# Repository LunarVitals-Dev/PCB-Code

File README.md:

## Overview
This project utilizes the Nordic nRF52840 and various sensors for data collection and analysis. Below are the sensors used, their datasheets, and their respective pin connections.

## Sensors and Connections

### On-Board Sensors (Connected to PCB)

1. **MLX90614 (Infrared Temperature Sensor)**  
   - [Datasheet](https://www.melexis.com/en/documents/documentation/datasheets/datasheet-mlx90614)  
   - **Connections:**
     - SDA -> P0.13
     - SCL -> P0.15
     - VDD -> VDD
     - GND -> GND

2. **MPU6050 (Accelerometer & Gyroscope)**  
   - [Datasheet](https://invensense.tdk.com/wp-content/uploads/2015/02/MPU-6000-Datasheet1.pdf)  
   - **Connections:**
     - SDA -> P1.10
     - SCL -> P1.15
     - VDD -> VDD
     - GND -> GND

3. **BMP280 (Barometric Pressure Sensor)**  
   - [Datasheet](https://cdn-shop.adafruit.com/datasheets/BST-BMP280-DS001-11.pdf)   
   - **Connections:**
     - SDI -> P0.13
     - SCK -> P0.15
     - SDO -> VDD
     - 3Vo -> VDD
     - GND -> GND

### External Sensors (Connected Externally)

4. **MAX30102 (Heart Rate & Blood Oxygen Sensor)**  
   - [Datasheet](https://www.analog.com/media/en/technical-documentation/data-sheets/max30102.pdf)  
   - **Connections:**
     - SDA -> P0.13
     - SCL -> P0.15
     - VDD -> VDD
     - GND -> GND

5. **SEN-11754 (Pulse Sensor)**  
   - [Datasheet](https://www.digikey.com/en/products/detail/sparkfun-electronics/SEN-11574/5762397)  
   - **Connections:**
     - ADC -> P0.29
     - VDD -> VDD
     - GND -> GND

6. **Conductive Rubber Cord (Stretch Sensor)**  
   - [Datasheet](https://www.verical.com/datasheet/adafruit-misc-sensors-519-5047094.pdf)  
   - **Connections:**
     - ADC -> P0.31
     - VDD -> VDD
     - GND -> GND

7. ADC: AIN5 - 0.29 (Pulse Sensor), AIN7 - 0.31 (Rubber Cord)

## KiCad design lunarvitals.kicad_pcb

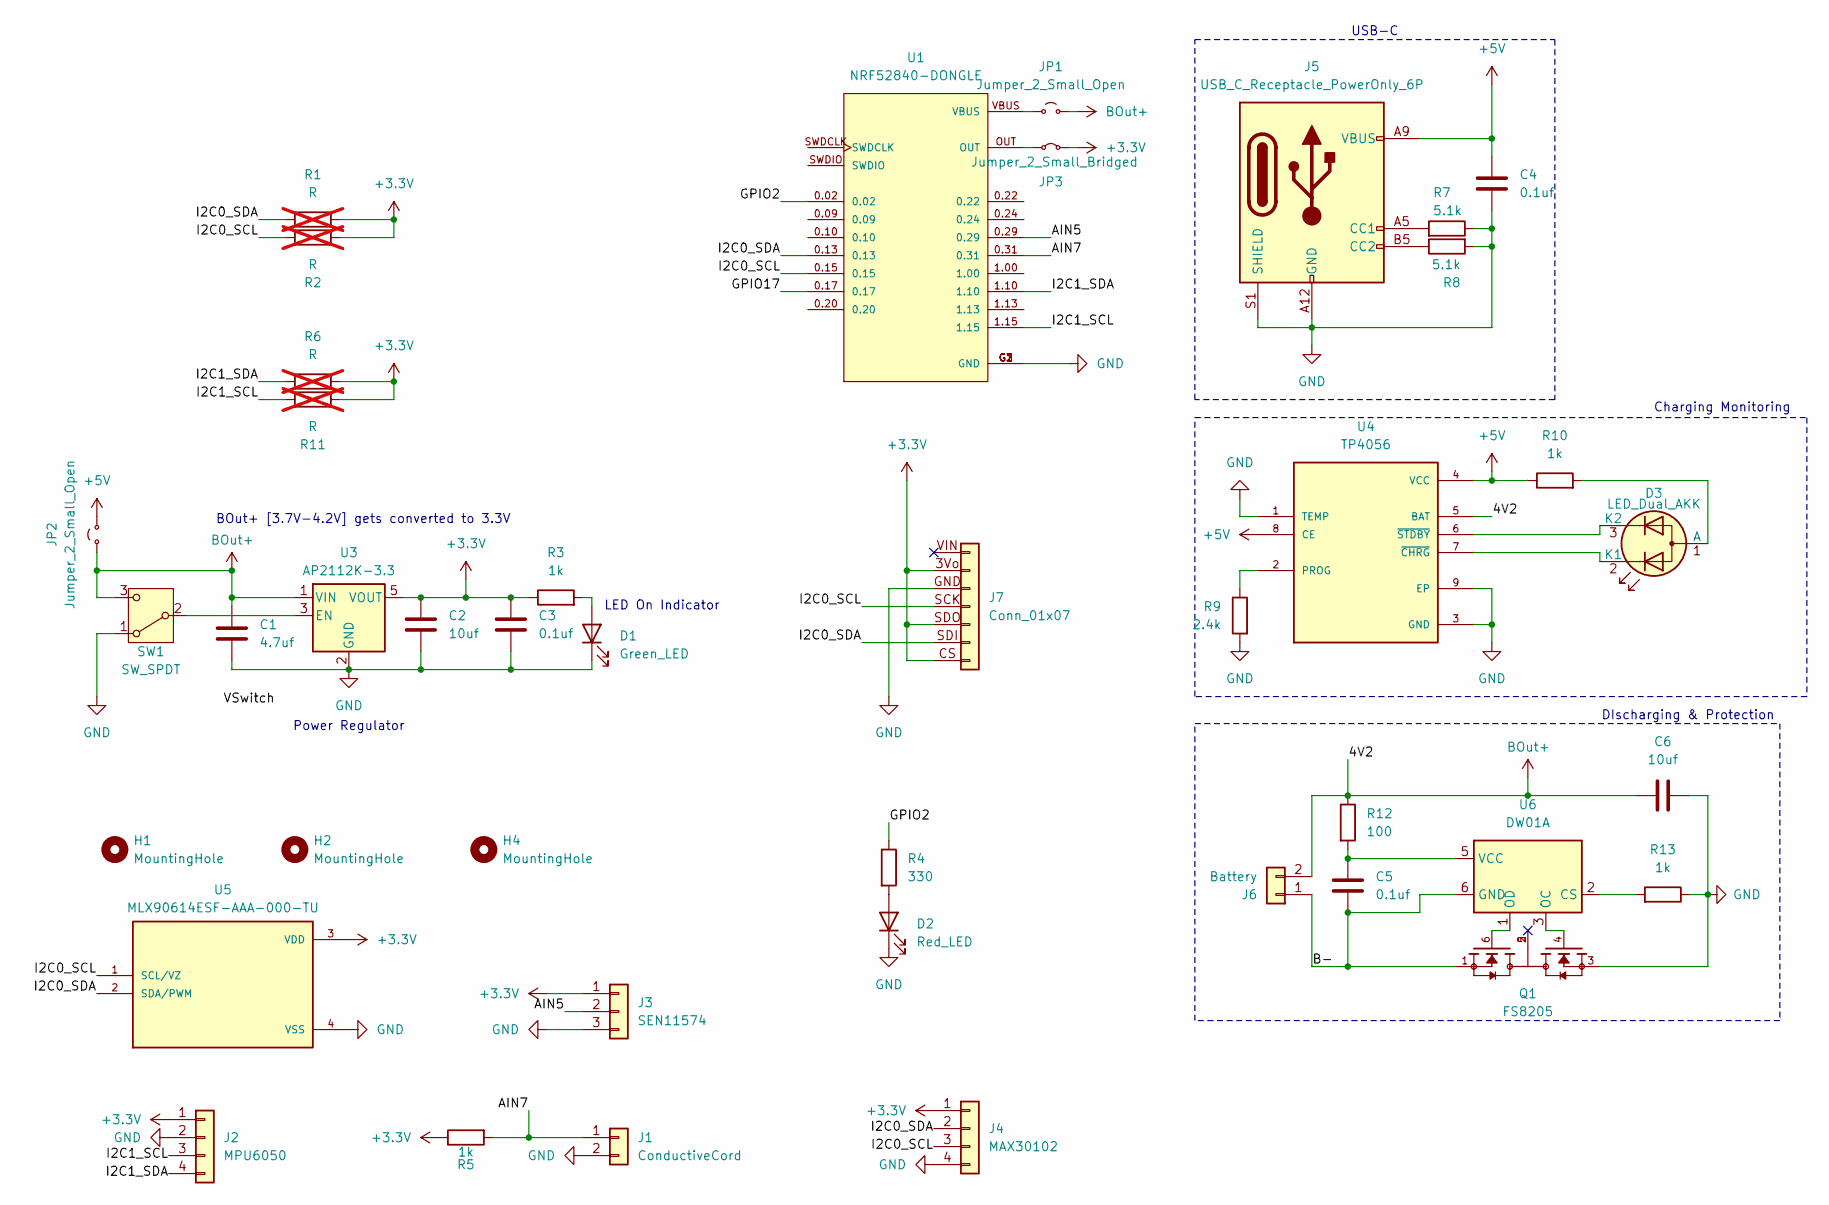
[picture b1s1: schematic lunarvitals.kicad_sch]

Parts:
C1: 4.7uf; C_0402_1005Metric; LCSC C23733
C2, C6: 10uf; C_0402_1005Metric; LCSC C15525
C3, C4, C5: 0.1uf; C_0402_1005Metric; LCSC C1525
D1: Green_LED; LED_D3.0mm
D2: Red_LED; LED_D3.0mm
D3: LED_Dual_AKK; LED_Kingbright_APBA3010SURKCGKC-GX_3x2x1mm; LCSC C5875732
H1, H2, H4: MountingHole; MountingHole_2.2mm_M2
J1: ConductiveCord; JST_XH_B2B-XH-A_1x02_P2.50mm_Vertical; LCSC C158012
J2: MPU6050; JST_XH_B4B-XH-A_1x04_P2.50mm_Vertical; LCSC C144395
J3: SEN11574; JST_XH_B3B-XH-A_1x03_P2.50mm_Vertical; LCSC C144394
J4: MAX30102; JST_XH_B4B-XH-A_1x04_P2.50mm_Vertical; LCSC C144395
J5: USB_C_Receptacle_PowerOnly_6P; USB_C_Receptacle_GCT_USB4125-xx-x-0190_6P_TopMnt_Horizontal; LCSC C668623
J6: Battery; SM02B-SRSS-TB_LF__SN_; LCSC C160402
J7: Conn_01x07; bmp280breakout
JP1, JP2: Jumper_2_Small_Open; SolderJumper-2_P1.3mm_Open_RoundedPad1.0x1.5mm
JP3: Jumper_2_Small_Bridged; SolderJumper-2_P1.3mm_Bridged_RoundedPad1.0x1.5mm
Q1: FS8205; SOT-23-6; PARTREV 1.9; LCSC C908265
R1, R2, R6, R11: R; R_0805_2012Metric_Pad1.20x1.40mm_HandSolder; not fitted
R3, R5, R10, R13: 1k; R_0402_1005Metric; LCSC C11702
R4: 330; R_0402_1005Metric; LCSC C12246
R7, R8: 5.1k; R_0402_1005Metric; LCSC C25905
R9: 2.4k; R_0402_1005Metric; LCSC C22940
R12: 100; R_0402_1005Metric; LCSC C25076
SW1: SW_SPDT; SW_Slide_SPDT_Angled_CK_OS102011MA1Q; LCSC C226259
U1: NRF52840-DONGLE; MODULE_NRF52840-DONGLE; PARTREV 1.1
U3: AP2112K-3.3; SOT-23-5; LCSC C3021085
U4: TP4056; SOP127P600X175-9N; LCSC C16581
U5: MLX90614ESF-AAA-000-TU; TO254P912H435-4; PARTREV 13
U6: DW01A; SOT-23-6; LCSC C2927799

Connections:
+3.3V: C2.1, C3.1, J2.1, J3.1, J4.1, J7.3Vo (Pin_2), J7.CS (Pin_7), J7.SDO (Pin_5), JP3.2 (B), R1.2, R2.1, R3.1, R5.1, R6.2, R11.1, U3.5 (VOUT), U5.3 (VDD)
+5V: C4.1, J5.A9 (VBUS), J5.B9 (VBUS), JP2.2 (B), R10.1, U4.4 (VCC), U4.8 (CE)
/AIN5: J3.2, U1.0.29
/AIN7: J1.1, R5.2, U1.0.31
/B-: C5.2, J6.1, Q1.1, U6.6 (GND)
/GPIO2: R4.1, U1.0.02
/GPIO17: U1.0.17
/I2C0_SCL: J4.3, J7.SCK (Pin_4), R2.2, U1.0.15, U5.1 (SCL/VZ)
/I2C0_SDA: J4.2, J7.SDI (Pin_6), R1.1, U1.0.13, U5.2 (SDA/PWM)
/I2C1_SCL: J2.3, R11.2, U1.1.15
/I2C1_SDA: J2.4, R6.1, U1.1.10
BOut+: C1.1, C6.1, J6.2, JP1.2 (B), JP2.1 (A), R12.1, SW1.3 (C), U3.1 (VIN), U4.5 (BAT)
GND: C1.2, C2.2, C3.2, C4.2, C6.2, D1.1 (K), D2.1 (K), J1.2, J2.2, J3.3, J4.4, J5.A12 (GND), J5.B12 (GND), J5.S1 (SHIELD), J7.GND (Pin_3), Q1.3, R7.1, R8.2, R9.2, R13.1, SW1.1 (A), U1.G1 (GND), U1.G2 (GND), U1.G3 (GND), U3.2 (GND), U4.1 (TEMP), U4.3 (GND), U4.9 (EP), U5.4 (VSS)
unnamed: D1.2 (A), R3.2
unnamed: D2.2 (A), R4.2
unnamed: D3.1 (A), R10.2
unnamed: D3.2 (K1), U4.7 (~CHRG)
unnamed: D3.3 (K2), U4.6 (~STDBY)
unnamed: J5.A5 (CC1), R7.2
unnamed: J5.B5 (CC2), R8.1
unnamed: JP1.1 (A), U1.VBUS
unnamed: JP3.1 (A), U1.OUT
unnamed: SW1.2 (B), U3.3 (EN)
unnamed: R9.1, U4.2 (PROG)
unnamed: R13.2, U6.2 (CS)
unnamed: Q1.4, U6.3 (OC)
unnamed: Q1.6, U6.1 (OD)
unnamed: C5.1, R12.2, U6.5 (VCC)

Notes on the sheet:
BOut+ [3.7V-4.2V] gets converted to 3.3V
DIscharging & Protection
USB-C
LED On Indicator
Power Regulator
Charging Monitoring

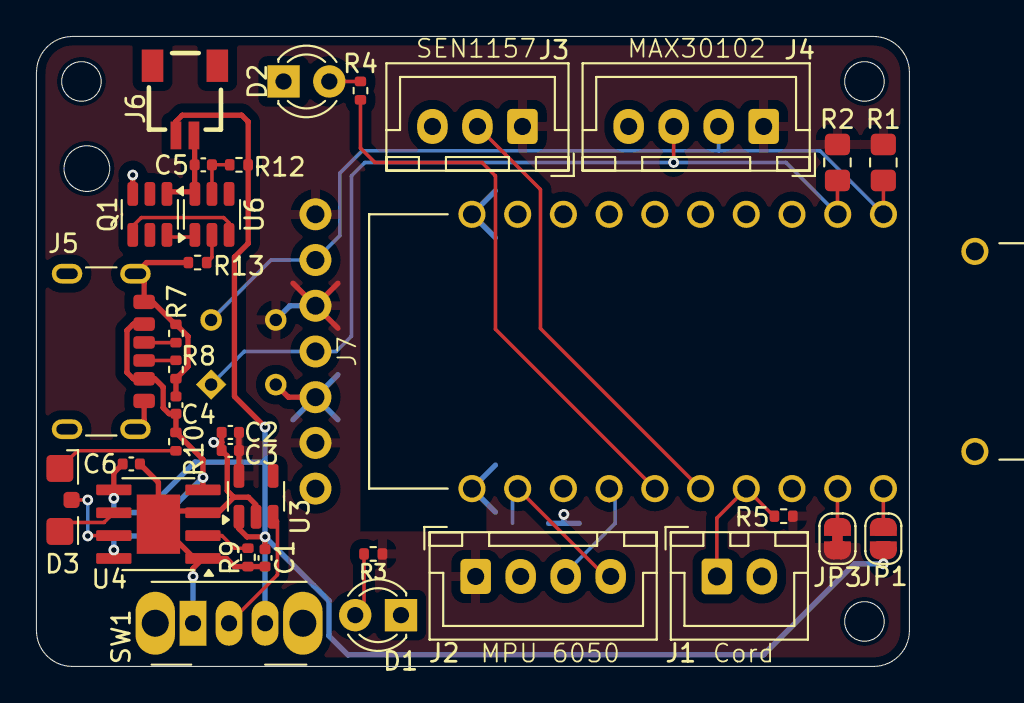
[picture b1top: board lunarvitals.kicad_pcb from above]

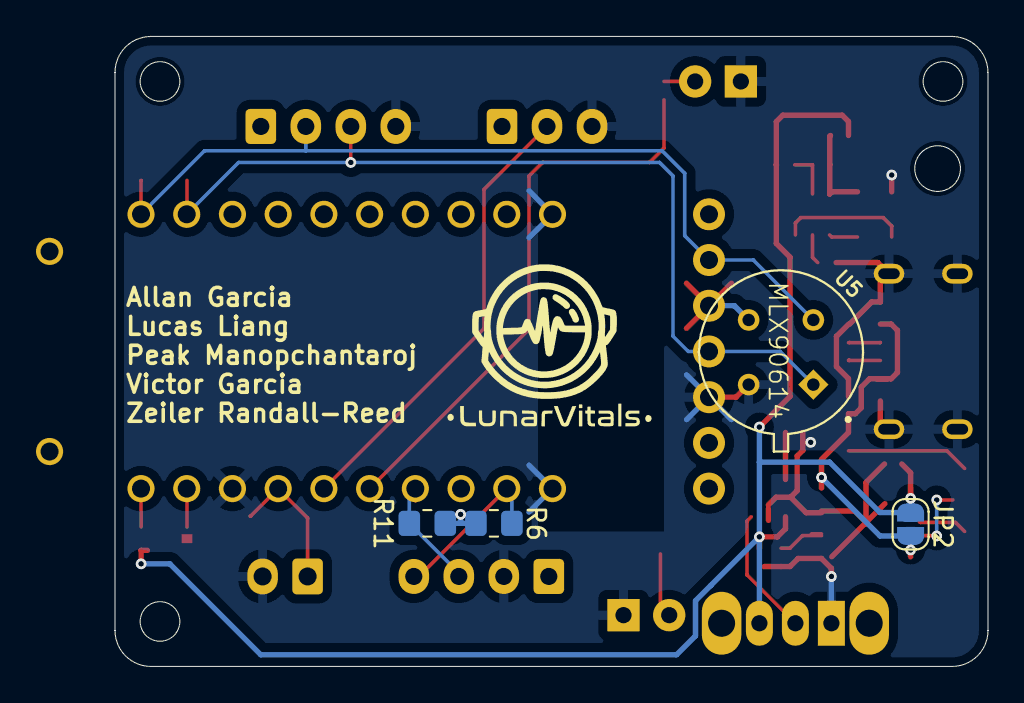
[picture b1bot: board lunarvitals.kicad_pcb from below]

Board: 2 copper layers, 48.5 x 35.0 mm, 42 parts (4 on the bottom side), 27 nets.

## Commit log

2025-02-05 initial code
2025-02-05 fixed adc readings
2025-02-05 updating code for MAX30102
2025-02-05 adding the initialization line for heart rate
2025-02-05 added sensors
2025-02-05 added zeiler code
2025-02-07 clean code
2025-02-07 all sensors output
2025-02-14 added json fixes
2025-02-14 changed pressure to int and in heptopascals
2025-02-18 added RGB and buttons
2025-02-19 blood oxygen is now integrated and finalized
2025-02-20 finalized some stuff
2025-02-21 bluetooth
2025-02-21 testing dongle with current code
2025-02-26 sensors still need reworking
2025-02-26 testing adc
2025-02-28 updated steps algo and created demo video
2025-03-11 PCB layout
2025-03-13 removed 2 voltage regulator on same 3.3v connection
2025-03-18 fix capacitor positioning
2025-03-18 minor fixes to BOM, remove THT parts from BOM
2025-03-18 add keepout for dongle antenna
2025-03-18 add scuffed mounting holes (better than none)
2025-04-10 testing PCB dongle now
2025-04-11 working version
2025-04-12 commented out blood oxygen and accelerometer is now on I2C1
2025-04-13 Remove dongle folder files except for zephyr.hex
2025-04-14 fixing the MAX30102 to only display heart rate instead of blood oxygen
2025-04-14 fixing MAX30102 to only display heart rate
2025-04-14 ADC is only working on pin 31 currently
2025-04-15 This bluetooth works on the nrf dongle using a specialized bluetooth code
2025-04-15 incorporated Victor's bluetooth code and fixed all warnings, still need to test with dongle
2025-04-15 only commiting zephyr.hex as build configuration is different for everyone
2025-04-16 changed loop to run every 100 msec and added an aggregate file where it combines all the sensors into 1 json and then transmit through bluetooth
2025-04-17 latest PCB working code as of 4/17
2025-04-19 PCB Updates
2025-04-22 add rate of change of steps
2025-04-23 pcb updates (logo, conductive cord, charging diodes, layout)
2025-04-23 fixed out of stock fs8205 and other small fixes
2025-04-23 LCSC part numbers
2025-04-23 include connectors in BOM
2025-04-24 final updates to PCB
2025-04-24 improved readability of code, took out all print statements, added rotation for arm swings
2025-04-24 added connector for MAX30102
2025-04-25 blood oxygen has now been integrated back into the code on I2C1
2025-04-25 shortened JSON messages
2025-04-26 latest working version
2025-04-30 will test accelerometer using the dev kit instead
2025-05-01 updating respiratory and accelerometer
2025-05-01 layout changes for screenshots
2025-05-06 add 3d models to repo
2025-05-07 fixed heart rate bpm
2025-05-09 bmp breakout board changes (unfinished)
2025-05-09 recalibrate accelerometer and pressure
2025-05-11 updated breathing rate to perform calculation on backend instead of frontend
2025-05-11 updated parameters for breathing rate
2025-05-12 LED changes and BMP model
2025-05-12 VRML export name change
2025-05-13 final changes
2025-05-13 remove via in pad
2025-05-13 added unpopulated pullup resistors for I2C
2025-05-13 reorient LED through holes
2025-05-13 fix jumper footprint and adjust charge indication led
2025-05-13 fill zone fix
2025-05-13 solder jumper pads in case of problems with various parts of the circuit
2025-05-14 fix contingency solder jumper connection
2025-05-14 changed JSON to CSV, MAX30102 now exits while loop so other sensors can continue to run in its absense
2025-05-14 fix silkscreen, exclude from POS attributes
2025-05-14 fix LED footprint
2025-05-14 bmp breakout path fix
2025-05-14 dual led location and routing fix
2025-05-14 move LED footprint anchor
2025-05-22 MAX30102 was put into I2C0 so moving the code to that
2025-05-23 implemented mutex locks on I2C0
2025-05-24 sensor accuracy modifications
